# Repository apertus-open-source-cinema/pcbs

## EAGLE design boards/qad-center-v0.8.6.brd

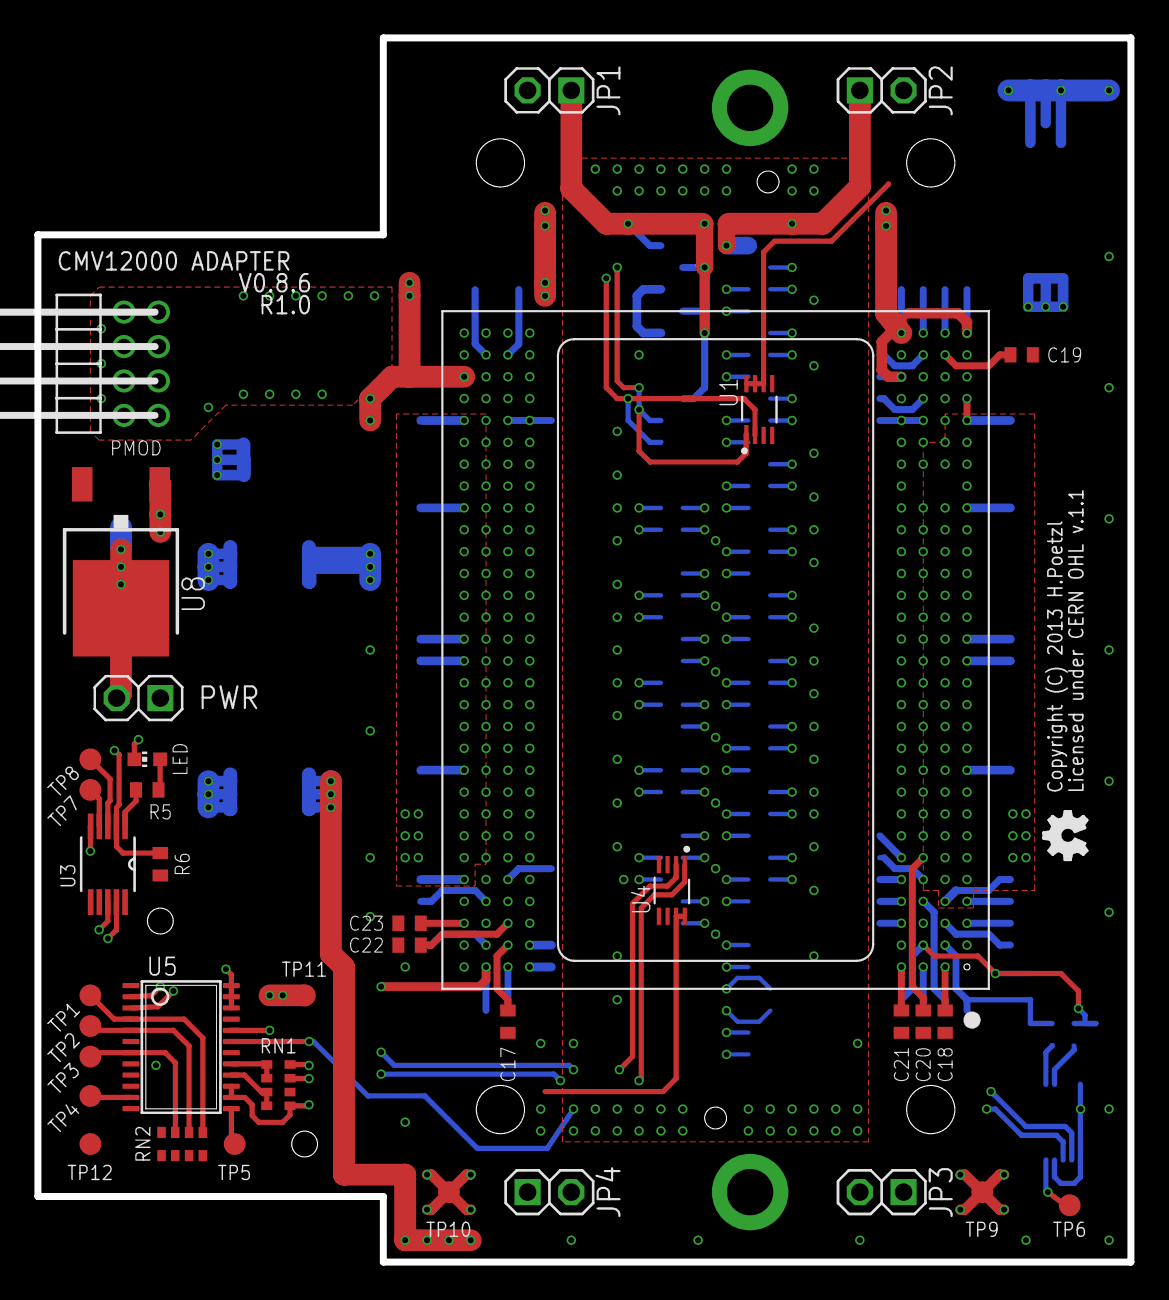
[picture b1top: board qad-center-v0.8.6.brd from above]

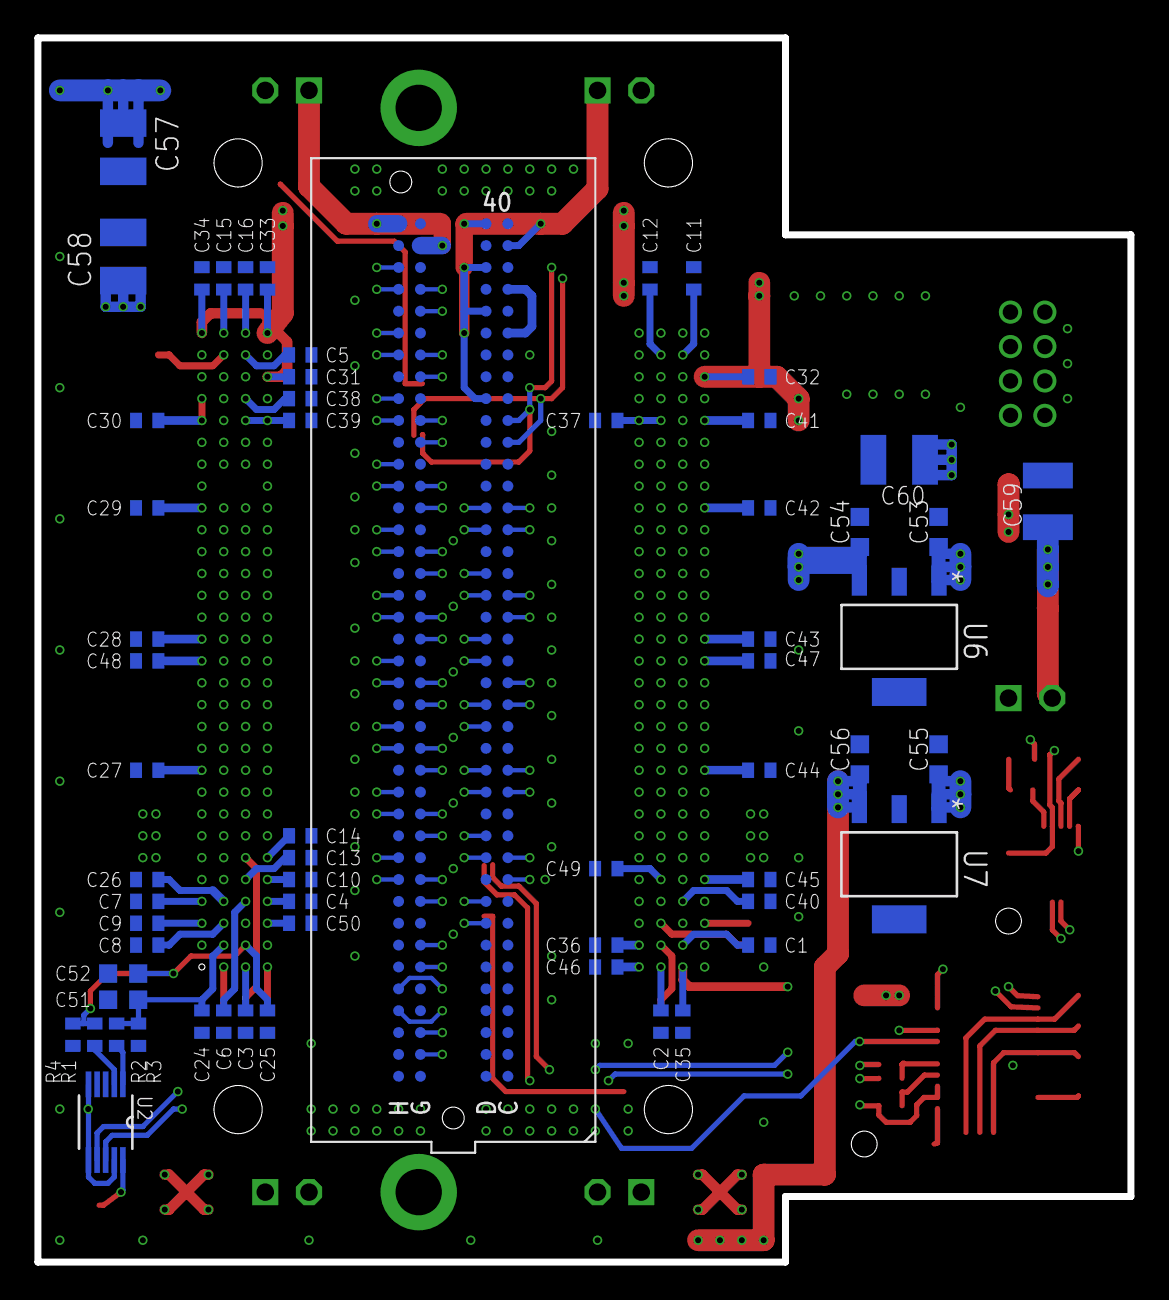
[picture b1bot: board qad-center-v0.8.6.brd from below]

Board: 4 copper layers, 63.5 x 71.1 mm, 98 parts (60 on the bottom side), 130 nets.

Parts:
C1, C2, C3, C4, C5, C6, C7, C8, C9, C10, C11, C12, C13, C14, C15, C16, C17, C18, C19, C20, C21, C22, C23, C24, C25, C26, C27, C28, C29, C30, C32, C33, C34, C35, C36, C37, C38, C39, C40, C41, C42, C43, C44, C45, C46, C47, C48, C49, C50: C0402
C31: 100n; C0402
C51, C52, C53, C54, C55, C56: 10u; C0603K
C57, C58: 100u; C1210
C59, C60: 100u; C1210K
JP1, JP2, JP3, JP4: 1X02-S
LED: RED; CHIP-LED0603
PMOD: PMOD-8; 2X04/90/2MM
PWR: 1X02-S
R1, R2: 1R; R0402
R3, R4: R0402
R5: 220R; R0402
R6: 10k; R0402
RN1, RN2: 10k; CAT16
TP1, TP2, TP3, TP4, TP5, TP6, TP7, TP8, TP9, TP10, TP11, TP12: TPB1,27; B1,27
U1, U4: LM75BGD; SOT996-2/3
U2: AD5647R; SOP50P490X110-10N
U3: PCA9537; TSSOP-10
U5: LM96080; TSSOP24
U6: MCP1826S-3002E/DB; SOT230P700X180-4N
U7: MCP1826S-1802E/DB; SOT230P700X180-4N
U8: AP1084TO252; TO252
U$1: CMV12000ANDON+LM; 10-30-07-237-400T4+LM
U$5: OSHW_FILLX100_NOTEXT
ZED1: FMC-LPC-ZED_NOCCZED; ASP-134604-01-ZED

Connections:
+1V8: C56.1, C57.1, JP2.2, JP3.2, JP4.2, U7.3
+1V8A: C26.1, C27.1, C28.1, C29.1, C30.1, C48.1, JP3.1, TP9.TP, U5.19, U$1.A10, U$1.A15, U$1.A16, U$1.A22, U$1.A26, U$1.A27, U$1.B4
+1V8B: C41.1, C42.1, C43.1, C44.1, C45.1, C46.1, C47.1, JP4.1, TP10.TP, U5.20, U$1.E1, U$1.H5, U$1.H10, U$1.H15, U$1.H16, U$1.H22, U$1.H26
+3V0: C31.1, C32.1, C33.1, C34.1, C35.1, C54.1, RN1.3, TP11.TP, U6.3, U$1.A30, U$1.D28, U$1.D30, U$1.G1, U$1.H28
+3V3: C17.1, C18.1, C19.1, C20.1, C21.1, C22.1, C23.1, C36.1, C37.1, C38.1, C39.1, C40.1, C49.1, C50.1, C53.1, C55.1, C58.1, C60.1, JP1.2, R6.1, RN1.2, RN2.2, RN2.3, RN2.4, TP12.TP, U1.6, U1.7, U1.8, U2.5, U2.6, U2.9, U3.6, U3.10, U4.7, U4.8, U5.1, U5.6, U5.9, U5.12, U6.1, U7.1, U8.2, U$1.C26, U$1.C27, U$1.D3, U$1.D26, U$1.E2, U$1.E26, U$1.F5, U$1.F26, U$1.G4
+5V: C59.1, PWR.2, U8.3
GND: C1.2, C2.2, C3.2, C4.2, C5.2, C6.2, C7.2, C8.2, C9.2, C10.2, C11.2, C12.2, C13.2, C14.2, C15.2, C16.2, C24.2, C25.2, C26.2, C27.2, C28.2, C29.2, C30.2, C31.2, C32.2, C33.2, C34.2, C35.2, C36.2, C37.2, C38.2, C39.2, C40.2, C41.2, C42.2, C43.2, C44.2, C45.2, C46.2, C47.2, C48.2, C49.2, C50.2, C51.2, C52.2, C53.2, C54.2, C55.2, C56.2, C57.2, C58.2, C59.2, C60.2, LED.C, PWR.1, R3.2, R4.2, RN1.1, RN1.4, U1.4, U1.5, U2.3, U2.4, U3.5, U4.4, U4.5, U4.6, U5.8, U5.14, U5.15, U5.18, U5.22, U5.23, U5.24, U6.2, U6.4, U7.2, U7.4, U8.1, U$1.A9, U$1.A21, U$1.A25, U$1.A28, U$1.A29, U$1.B5, U$1.B22, U$1.B26, U$1.B27, U$1.B28, U$1.C15, U$1.C16, U$1.C28, U$1.D2, U$1.D25, U$1.D27, U$1.D29, U$1.E3, U$1.E15, U$1.E16, U$1.E25, U$1.E27, U$1.F27, U$1.G5, U$1.H1, U$1.H6, U$1.H9, U$1.H21, U$1.H25, U$1.H27, ZED1.C1, ZED1.C4, ZED1.C5, ZED1.C8, ZED1.C9, ZED1.C12, ZED1.C13, ZED1.C16, ZED1.C17, ZED1.C20, ZED1.C21, ZED1.C24, ZED1.C25, ZED1.C28, ZED1.C29, ZED1.C32, ZED1.C33, ZED1.C36, ZED1.C38, ZED1.C40, ZED1.D2, ZED1.D3, ZED1.D6, ZED1.D7, ZED1.D10, ZED1.D13, ZED1.D16, ZED1.D19, ZED1.D22, ZED1.D25, ZED1.D28, ZED1.D37, ZED1.D39, ZED1.G1, ZED1.G4, ZED1.G5, ZED1.G8, ZED1.G11, ZED1.G14, ZED1.G17, ZED1.G20, ZED1.G23, ZED1.G26, ZED1.G29, ZED1.G32, ZED1.G35, ZED1.G38, ZED1.G40, ZED1.H3, ZED1.H6, ZED1.H9, ZED1.H12, ZED1.H15, ZED1.H18, ZED1.H21, ZED1.H24, ZED1.H27, ZED1.H30, ZED1.H33, ZED1.H36, ZED1.H39
unnamed: C17.2, U$1.F2
unnamed: C18.2, U$1.B1
unnamed: C19.2, U$1.B29
unnamed: C20.2, U$1.C6
unnamed: C21.2, U$1.D1
unnamed: C22.2, U$1.F3
unnamed: C23.2, U$1.H3
unnamed: C1.1, U$1.G2
unnamed: C2.1, U$1.F1
unnamed: C3.1, U$1.C1
unnamed: C4.1, U$1.D4
unnamed: C5.1, U$1.C29
unnamed: C6.1, U$1.C4
unnamed: C7.1, U$1.A4
unnamed: C8.1, U$1.B3
unnamed: C9.1, U$1.A3
unnamed: C10.1, U$1.D5
unnamed: C11.1, U$1.G29
unnamed: C12.1, U$1.F29
unnamed: C13.1, U$1.C5
unnamed: C14.1, U$1.D6
unnamed: C15.1, U$1.B30
unnamed: C16.1, U$1.C30
unnamed: U$1.B6, ZED1.H11
unnamed: U$1.B7, ZED1.H10
unnamed: PMOD.1, U$1.F28
unnamed: U$1.D7, ZED1.D12
unnamed: U$1.D8, ZED1.D11
unnamed: PMOD.8, U$1.H29
unnamed: PMOD.2, U$1.E28
unnamed: PMOD.7, U$1.G28
unnamed: PMOD.10, U$1.E30
unnamed: PMOD.4, U$1.G30
unnamed: U$1.B8, ZED1.H14
unnamed: U$1.C9, ZED1.D15
unnamed: U$1.C10, ZED1.D14
unnamed: ZED1.C35, ZED1.C37
unnamed: JP1.1, ZED1.C39, ZED1.D32, ZED1.D36, ZED1.D38, ZED1.D40
unnamed: JP2.1, ZED1.G39, ZED1.H40
unnamed: R1.2, U2.2
unnamed: U$1.G10, ZED1.G13
unnamed: U$1.A11, ZED1.D18
unnamed: U$1.A12, ZED1.D17
unnamed: U$1.C11, ZED1.H17
unnamed: U$1.C12, ZED1.H16
unnamed: U$1.A13, ZED1.D21
unnamed: U$1.A14, ZED1.D20
unnamed: U$1.D13, ZED1.H20
unnamed: U$1.D14, ZED1.H19
unnamed: U$1.F16, ZED1.G22
unnamed: U$1.F17, ZED1.G21
unnamed: U$1.A17, ZED1.H26
unnamed: U$1.A18, ZED1.H25
unnamed: U$1.C17, ZED1.D24
unnamed: U$1.C18, ZED1.D23
unnamed: U$1.A19, ZED1.H29
unnamed: U$1.A20, ZED1.H28
unnamed: U$1.C19, ZED1.D27
unnamed: U$1.C20, ZED1.D26
unnamed: U$1.D21, ZED1.H32
unnamed: U$1.D22, ZED1.H31
unnamed: U$1.A23, ZED1.H35
unnamed: U$1.A24, ZED1.H34
unnamed: U$1.B24, ZED1.H38
unnamed: U$1.B25, ZED1.H37
unnamed: U$1.D15, ZED1.H23
unnamed: U$1.D16, ZED1.H22
unnamed: U$1.G22, ZED1.G34
unnamed: U$1.G23, ZED1.G33
unnamed: U$1.E22, ZED1.G30
unnamed: U$1.E21, ZED1.G31
unnamed: U$1.F21, ZED1.G27
unnamed: U$1.F20, ZED1.G28
unnamed: U$1.E20, ZED1.C26
unnamed: U$1.E19, ZED1.C27
unnamed: U$1.F19, ZED1.G24
unnamed: U$1.F18, ZED1.G25
unnamed: U$1.E18, ZED1.C22
unnamed: U$1.E17, ZED1.C23
unnamed: U$1.H23, ZED1.G37
unnamed: U$1.H24, ZED1.G36
unnamed: U$1.G15, ZED1.G18
unnamed: U$1.G14, ZED1.G19
unnamed: U$1.H14, ZED1.C18
unnamed: U$1.H13, ZED1.C19
unnamed: U$1.G13, ZED1.G15
unnamed: U$1.G12, ZED1.G16
unnamed: U$1.H12, ZED1.C14
unnamed: U$1.H11, ZED1.C15
unnamed: U$1.G11, ZED1.G12
unnamed: U$1.B9, ZED1.H13
unnamed: U$1.F9, ZED1.C10
unnamed: U$1.F8, ZED1.C11
unnamed: U$1.E8, ZED1.G9
unnamed: U$1.E7, ZED1.G10
unnamed: U$1.F7, ZED1.G6
unnamed: U$1.F6, ZED1.G7
unnamed: U$1.E5, ZED1.H5
unnamed: U$1.E6, ZED1.H4
unnamed: U$1.G6, ZED1.G3
unnamed: U$1.G7, ZED1.G2
unnamed: U$1.A5, ZED1.D9
unnamed: U$1.A6, ZED1.D8
unnamed: PMOD.9, U$1.H30
unnamed: PMOD.3, U$1.E29
unnamed: RN2.5, TP1.TP, U5.4
unnamed: R6.2, U3.2, U$1.F30
unnamed: R5.1, U3.1
unnamed: RN2.6, TP2.TP, U5.5
unnamed: TP8.TP, U3.3
unnamed: TP7.TP, U3.4
unnamed: RN1.5, RN1.6, U5.17
unnamed: RN2.7, TP3.TP, U5.7
unnamed: TP4.TP, U5.11
unnamed: TP5.TP, U5.13
unnamed: RN1.7, RN1.8, U5.16
unnamed: R2.2, U2.1
unnamed: LED.A, R5.2
unnamed: TP6.TP, U2.10
SCL: U1.2, U2.7, U3.8, U4.2, U5.3, ZED1.C30
SDA: U1.1, U2.8, U3.9, U4.1, U5.2, ZED1.C31
VTREF: C24.1, C51.1, R2.1, R3.1, U$1.B2
VTSIG: C25.1, C52.1, R1.1, R4.1, U$1.C2

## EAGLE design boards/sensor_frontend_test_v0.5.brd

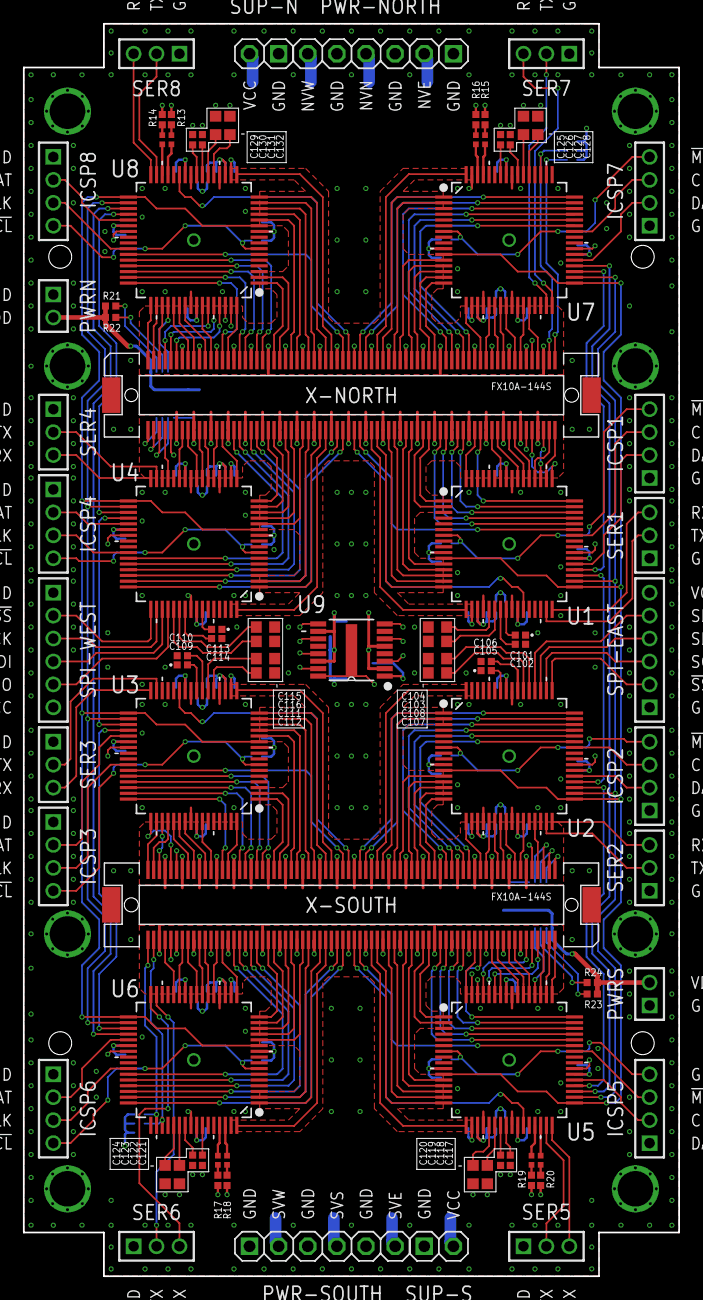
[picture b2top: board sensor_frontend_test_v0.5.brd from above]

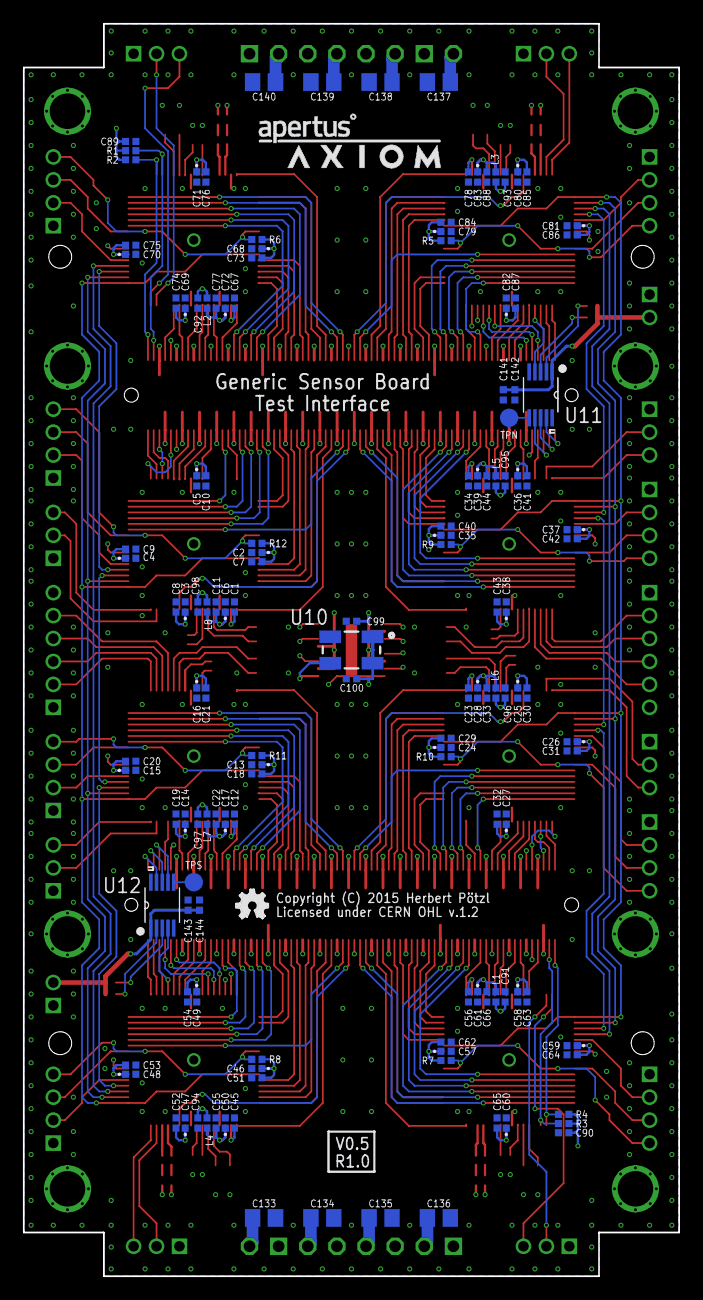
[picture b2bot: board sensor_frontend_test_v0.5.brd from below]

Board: 4 copper layers, 57.1 x 109.2 mm, 223 parts (140 on the bottom side), 345 nets.

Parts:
C1, C2, C3, C4, C5, C6, C7, C8, C9, C10, C11, C12, C13, C14, C15, C16, C17, C18, C19, C20, C21, C22, C23, C24, C25, C26, C27, C28, C29, C30, C31, C32, C33, C34, C35, C36, C37, C38, C39, C40, C41, C42, C43, C44, C45, C46, C47, C48, C49, C50, C51, C52, C53, C54, C55, C56, C57, C58, C59, C60, C61, C62, C63, C64, C65, C66, C67, C68, C69, C70, C71, C72, C73, C74, C75, C76, C77, C78, C79, C80, C81, C82, C83, C84, C85, C86, C87, C88, C89, C90, C91, C92, C93, C94, C95, C96, C97, C98, C99, C100, C101, C102, C105, C106, C109, C110, C113, C114, C117, C118, C121, C122, C125, C126, C129, C130, C141, C142, C143, C144: 0402-B
C103, C104, C107, C108, C111, C112, C115, C116, C119, C120, C123, C124, C127, C128, C131, C132: 0603-B
C133, C134, C135, C136, C137, C138, C139, C140: 0805-A
ICSP1, ICSP2, ICSP3, ICSP4, ICSP5, ICSP6, ICSP7, ICSP8: 1X04M
L1, L2, L3, L4, L5, L6, L7, L8: 0402-B
LED1, LED2, LED3, LED4: DUAL-LED-0404; 0404
LOGO1: OSHW_LOGO_FILLX0100-NT; OSHW_FILLX100_NOTEXT
PWR-NORTH: 1X06-S
PWR-SOUTH: 1X06-S
PWRN: 1X02M
PWRS: 1X02M
R1, R2, R3, R4, R5, R6, R7, R8, R9, R10, R11, R12, R13, R14, R15, R16, R17, R18, R19, R20, R21, R22, R23, R24: 0402-B
SER1, SER2, SER3, SER4, SER5, SER6, SER7, SER8: 1X03M
SPI-EAST: 1X06M
SPI-WEST: 1X06M
SUP-N: 1X02-S
SUP-S: 1X02-S
TPN: TPTP16R; TP16R
TPS: TPTP16R; TP16R
U1, U2, U3, U4, U5, U6, U7, U8: PIC16F1526-I/PT; QFP50P1200X1200X120-64N
U9: SI53365; SOP65P640X120-16N
U10: OSCILLATOR5X3-PIN1-INDICATED; CRYSTAL-OSC-SMD-5X3
U11, U12: MCP4728-E/UN; SOP50P490X110-10N
U$2: APERTUS_LOGO334X100; APERTUS_LOGO_334X100
U$3: AXIOM_LOGO525X80; AXIOM_LOGO_525X80
X-NORTH: FX10-144S; FX10A-144S
X-SOUTH: FX10-144S; FX10A-144S

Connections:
!E_SS: U1.11, U1.33, U2.11, U2.33, U5.11, U5.33, U7.11, U7.33
!LDAC_N: U8.52, U11.4
!LDAC_S: U5.52, U12.4
!MCLR1!: ICSP1.4, R12.2, U1.7
!MCLR2!: ICSP2.4, R11.2, U2.7
!MCLR3!: ICSP3.4, R10.2, U3.7
!MCLR4!: ICSP4.4, R9.2, U4.7
!MCLR5!: ICSP5.4, R8.2, U5.7
!MCLR6!: ICSP6.4, R7.2, U6.7
!MCLR7!: ICSP7.4, R6.2, U7.7
!MCLR8!: ICSP8.4, R5.2, U8.7
!W_SS: U3.11, U3.33, U4.11, U4.33, U6.11, U6.33, U8.11, U8.33
AVCC1: C6.1, C11.1, L8.2, U1.19
AVCC2: C17.1, C22.1, L7.2, U2.19
AVCC3: C28.1, C33.1, L6.2, U3.19
AVCC4: C39.1, C44.1, L5.2, U4.19
AVCC5: C50.1, C55.1, L4.2, U5.19
AVCC6: C61.1, C66.1, L1.2, U6.19
AVCC7: C72.1, C77.1, L2.2, U7.19
AVCC8: C83.1, C88.1, L3.2, U8.19
CAP1A: C101.1, U1.24
CAP1B: C102.1, U1.23
CAP1C: C103.1, U1.22
CAP1D: C104.1, U1.21
CAP2A: C105.1, U2.58
CAP2B: C106.1, U2.55
CAP2C: C107.1, U2.54
CAP2D: C108.1, U2.53
CAP3A: C109.1, U3.24
CAP3B: C110.1, U3.23
CAP3C: C111.1, U3.22
CAP3D: C112.1, U3.21
CAP4A: C113.1, U4.58
CAP4B: C114.1, U4.55
CAP4C: C115.1, U4.54
CAP4D: C116.1, U4.53
CAP5A: C117.1, U5.24
CAP5B: C118.1, U5.23
CAP5C: C119.1, U5.22
CAP5D: C120.1, U5.21
CAP6A: C121.1, U6.58
CAP6B: C122.1, U6.55
CAP6C: C123.1, U6.54
CAP6D: C124.1, U6.53
CAP7A: C125.1, U7.58
CAP7B: C126.1, U7.55
CAP7C: C127.1, U7.54
CAP7D: C128.1, U7.53
CAP8A: C129.1, U8.24
CAP8B: C130.1, U8.23
CAP8C: C131.1, U8.22
CAP8D: C132.1, U8.21
CLKIN1: U1.39, U9.8
CLKIN2: U2.39, U9.16
CLKIN3: U3.39, U9.15
CLKIN4: U4.39, U9.9
CLKIN5: U5.39, U9.3
CLKIN6: U6.39, U9.13
CLKIN7: U7.39, U9.6
CLKIN8: U8.39, U9.11
E_SCK: U1.34, U2.34, U5.34, U7.34
E_SD_17: U1.36, U7.35
E_SD_21: U1.35, U2.36
E_SD_52: U2.35, U5.36
E_SD_75: U5.35, U7.36
GND: C1.2, C2.2, C3.2, C4.2, C5.2, C6.2, C7.2, C8.2, C9.2, C10.2, C11.2, C12.2, C13.2, C14.2, C15.2, C16.2, C17.2, C18.2, C19.2, C20.2, C21.2, C22.2, C23.2, C24.2, C25.2, C26.2, C27.2, C28.2, C29.2, C30.2, C31.2, C32.2, C33.2, C34.2, C35.2, C36.2, C37.2, C38.2, C39.2, C40.2, C41.2, C42.2, C43.2, C44.2, C45.2, C46.2, C47.2, C48.2, C49.2, C50.2, C51.2, C52.2, C53.2, C54.2, C55.2, C56.2, C57.2, C58.2, C59.2, C60.2, C61.2, C62.2, C63.2, C64.2, C65.2, C66.2, C67.2, C68.2, C69.2, C70.2, C71.2, C72.2, C73.2, C74.2, C75.2, C76.2, C77.2, C78.2, C79.2, C80.2, C81.2, C82.2, C83.2, C84.2, C85.2, C86.2, C87.2, C88.2, C89.2, C90.2, C91.2, C92.2, C93.2, C94.2, C95.2, C96.2, C97.2, C98.2, C99.2, C100.2, C101.2, C102.2, C103.2, C104.2, C105.2, C106.2, C107.2, C108.2, C109.2, C110.2, C111.2, C112.2, C113.2, C114.2, C115.2, C116.2, C117.2, C118.2, C119.2, C120.2, C121.2, C122.2, C123.2, C124.2, C125.2, C126.2, C127.2, C128.2, C129.2, C130.2, C131.2, C132.2, C133.2, C134.2, C135.2, C136.2, C137.2, C138.2, C139.2, C140.2, C141.2, C142.2, C143.2, C144.2, ICSP1.1, ICSP2.1, ICSP3.1, ICSP4.1, ICSP5.1, ICSP6.1, ICSP7.1, ICSP8.1, PWR-NORTH.1, PWR-NORTH.3, PWR-NORTH.5, PWR-SOUTH.1, PWR-SOUTH.3, PWR-SOUTH.5, PWRN.1, PWRS.1, SER1.1, SER2.1, SER3.1, SER4.1, SER5.1, SER6.1, SER7.1, SER8.1, SPI-EAST.1, SPI-WEST.1, SUP-N.1, SUP-S.1, U1.9, U1.20, U1.25, U1.41, U1.56, U2.9, U2.20, U2.25, U2.41, U2.56, U3.9, U3.20, U3.25, U3.41, U3.56, U4.9, U4.20, U4.25, U4.41, U4.56, U5.9, U5.20, U5.25, U5.41, U5.56, U6.9, U6.20, U6.25, U6.41, U6.56, U7.9, U7.20, U7.25, U7.41, U7.56, U7.63, U8.9, U8.20, U8.25, U8.41, U8.56, U9.4, U9.7, U9.12, U10.2, U11.10, U12.10, X-NORTH.12, X-NORTH.18, X-NORTH.24, X-NORTH.30, X-NORTH.36, X-NORTH.42, X-NORTH.43, X-NORTH.48, X-NORTH.54, X-NORTH.60, X-NORTH.66, X-NORTH.72, X-NORTH.78, X-NORTH.84, X-NORTH.90, X-NORTH.96, X-NORTH.102, X-NORTH.103, X-NORTH.108, X-NORTH.114, X-NORTH.120, X-NORTH.126, X-NORTH.132, X-NORTH.138, X-NORTH.139, X-SOUTH.12, X-SOUTH.18, X-SOUTH.24, X-SOUTH.30, X-SOUTH.36, X-SOUTH.42, X-SOUTH.43, X-SOUTH.48, X-SOUTH.54, X-SOUTH.60, X-SOUTH.66, X-SOUTH.72, X-SOUTH.78, X-SOUTH.84, X-SOUTH.90, X-SOUTH.96, X-SOUTH.102, X-SOUTH.103, X-SOUTH.108, X-SOUTH.114, X-SOUTH.120, X-SOUTH.126, X-SOUTH.132, X-SOUTH.138, X-SOUTH.139
ICSPCLK1: ICSP1.3, U1.42
ICSPCLK2: ICSP2.3, U2.42
ICSPCLK3: ICSP3.3, U3.42
ICSPCLK4: ICSP4.3, U4.42
ICSPCLK5: ICSP5.3, U5.42
ICSPCLK6: ICSP6.3, U6.42
ICSPCLK7: ICSP7.3, U7.42
ICSPCLK8: ICSP8.3, U8.42
ICSPDAT1: ICSP1.2, U1.37
ICSPDAT2: ICSP2.2, U2.37
ICSPDAT3: ICSP3.2, U3.37
ICSPDAT4: ICSP4.2, U4.37
ICSPDAT5: ICSP5.2, U5.37
ICSPDAT6: ICSP6.2, U6.37
ICSPDAT7: ICSP7.2, U7.37
ICSPDAT8: ICSP8.2, U8.37
LED5: LED4.4, U5.29
LED5B: LED4.3, U5.30
LED6: LED3.4, U6.61
LED6B: LED3.3, U6.62
LED7: LED2.4, U7.61
LED7B: LED2.3, U7.62
LED8: LED1.4, U8.29
LED8B: LED1.3, U8.30
N00_N: U4.24, X-NORTH.16
N00_P: U4.27, X-NORTH.14
N01_N: U8.54, X-NORTH.17
N01_P: U8.53, X-NORTH.15
N02_N: U4.22, X-NORTH.22
N02_P: U4.23, X-NORTH.20
N03_N: U8.58, X-NORTH.23
N03_P: U8.55, X-NORTH.21
N04_N: U4.17, X-NORTH.28
N04_P: U4.21, X-NORTH.26
N05_N: U8.64, X-NORTH.29
N05_P: U8.48, X-NORTH.27
N06_N: U4.44, X-NORTH.34
N06_P: U4.43, X-NORTH.32
N07_N: U8.46, X-NORTH.35
N07_P: U8.47, X-NORTH.33
N08_N: U4.46, X-NORTH.40
N08_P: U4.45, X-NORTH.38
N09_N: U8.44, X-NORTH.41
N09_P: U8.45, X-NORTH.39
N10_N: U4.15, X-NORTH.46
N10_P: U4.16, X-NORTH.44
N11_N: U8.2, X-NORTH.47
N11_P: U8.1, X-NORTH.45
N12_N: U4.13, X-NORTH.52
N12_P: U4.14, X-NORTH.50
N13_N: U8.13, X-NORTH.53
N13_P: U8.12, X-NORTH.51
N14_N: U4.2, X-NORTH.58
N14_P: U4.12, X-NORTH.56
N15_N: U8.15, X-NORTH.59
N15_P: U8.14, X-NORTH.57
N16_N: U4.64, X-NORTH.64
N16_P: U4.1, X-NORTH.62
N17_N: U8.17, X-NORTH.65
N17_P: U8.16, X-NORTH.63
N18_N: U4.48, X-NORTH.70
N18_P: U4.47, X-NORTH.68
N19_N: U8.27, X-NORTH.71
N19_P: U8.43, X-NORTH.69
N20_N: U1.43, X-NORTH.76
N20_P: U1.27, X-NORTH.74
N21_N: U7.47, X-NORTH.77
N21_P: U7.48, X-NORTH.75
N22_N: U1.16, X-NORTH.82
N22_P: U1.17, X-NORTH.80
N23_N: U7.1, X-NORTH.83
N23_P: U7.64, X-NORTH.81
N24_N: U1.14, X-NORTH.88
N24_P: U1.15, X-NORTH.86
N25_N: U7.12, X-NORTH.89
N25_P: U7.2, X-NORTH.87
N26_N: U1.12, X-NORTH.94
N26_P: U1.13, X-NORTH.92
N27_N: U7.14, X-NORTH.95
N27_P: U7.13, X-NORTH.93
N28_N: U1.1, X-NORTH.100
N28_P: U1.2, X-NORTH.98
N29_N: U7.16, X-NORTH.101
N29_P: U7.15, X-NORTH.99
N30_N: U1.45, X-NORTH.106
N30_P: U1.44, X-NORTH.104
N31_N: U7.45, X-NORTH.107
N31_P: U7.46, X-NORTH.105
N32_N: U1.47, X-NORTH.112
N32_P: U1.46, X-NORTH.110
N33_N: U7.43, X-NORTH.113
N33_P: U7.44, X-NORTH.111
N34_N: U1.48, X-NORTH.118
N34_P: U1.64, X-NORTH.116
N35_N: U7.21, X-NORTH.119
N35_P: U7.17, X-NORTH.117
N36_N: U1.55, X-NORTH.124
N36_P: U1.58, X-NORTH.122
N37_N: U7.23, X-NORTH.125
N37_P: U7.22, X-NORTH.123
N38_N: U1.53, X-NORTH.130
N38_P: U1.54, X-NORTH.128
N39_N: U7.27, X-NORTH.131
N39_P: U7.24, X-NORTH.129
unnamed: C45.1, U5.18
unnamed: U9.1, U10.3
unnamed: TPS.TP, U12.6
unnamed: C1.1, U1.18
unnamed: LED1.1, R13.2
unnamed: LED1.2, R14.2
unnamed: LED2.1, R15.2
unnamed: LED2.2, R16.2
unnamed: LED3.1, R17.2
unnamed: LED3.2, R18.2
unnamed: LED4.1, R19.2
unnamed: LED4.2, R20.2
unnamed: TPN.TP, U11.6
unnamed: C56.1, U6.18
unnamed: C12.1, U2.18
unnamed: C23.1, U3.18
unnamed: C34.1, U4.18
unnamed: C67.1, U7.18
unnamed: C78.1, U8.18
N_CHK_EN: U4.29, X-NORTH.8
N_CHK_V: C141.1, C142.1, PWRN.2, R21.1, R22.1, U11.1, X-NORTH.10
N_I2C_EN: U7.28, X-NORTH.137
N_SCK: U1.50, X-NORTH.144
N_SCL: R2.2, U7.50, X-NORTH.143
N_SDA: R1.2, U7.51, X-NORTH.141
N_SDI: U1.51, X-NORTH.140
N_SDO: U1.52, X-NORTH.142
N_SPI_EN: U1.49, X-NORTH.136
N_VE: C140.1, PWR-NORTH.2, X-NORTH.109, X-NORTH.115, X-NORTH.127, X-NORTH.133
N_VE_CV: U11.7, X-NORTH.6
N_VE_OV: U8.51, X-NORTH.5
N_VE_UV: U8.61, X-NORTH.11
N_VN: C139.1, PWR-NORTH.4, X-NORTH.49, X-NORTH.55, X-NORTH.61, X-NORTH.67, X-NORTH.79, X-NORTH.85, X-NORTH.91, X-NORTH.97
N_VN_CV: U11.8, X-NORTH.4
N_VN_OV: U8.50, X-NORTH.3
N_VN_UV: U8.60, X-NORTH.9
N_VW: C138.1, PWR-NORTH.6, X-NORTH.13, X-NORTH.19, X-NORTH.31, X-NORTH.37
N_VW_CV: U11.9, X-NORTH.2
N_VW_OV: U8.49, X-NORTH.1
N_VW_UV: U8.59, X-NORTH.7
RX1: SER1.3, U1.32
RX2: SER2.3, U2.32
RX3: SER3.3, U3.32
RX4: SER4.3, U4.32
RX5: SER5.3, U5.32
RX6: SER6.3, U6.32
RX7: SER7.3, U7.32
RX8: SER8.3, U8.32
S00_N: U2.24, X-SOUTH.16
S00_P: U2.27, X-SOUTH.14
S01_N: U5.54, X-SOUTH.17
S01_P: U5.53, X-SOUTH.15
S02_N: U2.22, X-SOUTH.22
S02_P: U2.23, X-SOUTH.20
S03_N: U5.58, X-SOUTH.23
S03_P: U5.55, X-SOUTH.21
S04_N: U2.17, X-SOUTH.28
S04_P: U2.21, X-SOUTH.26
S05_N: U5.64, X-SOUTH.29
S05_P: U5.48, X-SOUTH.27
S06_N: U2.44, X-SOUTH.34
S06_P: U2.43, X-SOUTH.32
S07_N: U5.46, X-SOUTH.35
S07_P: U5.47, X-SOUTH.33
S08_N: U2.46, X-SOUTH.40
S08_P: U2.45, X-SOUTH.38
S09_N: U5.44, X-SOUTH.41
S09_P: U5.45, X-SOUTH.39
S10_N: U2.15, X-SOUTH.46
S10_P: U2.16, X-SOUTH.44
S11_N: U5.2, X-SOUTH.47
S11_P: U5.1, X-SOUTH.45
S12_N: U2.13, X-SOUTH.52
S12_P: U2.14, X-SOUTH.50
S13_N: U5.13, X-SOUTH.53
S13_P: U5.12, X-SOUTH.51
S14_N: U2.2, X-SOUTH.58
S14_P: U2.12, X-SOUTH.56
S15_N: U5.15, X-SOUTH.59
S15_P: U5.14, X-SOUTH.57
S16_N: U2.64, X-SOUTH.64
S16_P: U2.1, X-SOUTH.62
S17_N: U5.17, X-SOUTH.65
S17_P: U5.16, X-SOUTH.63
S18_N: U2.48, X-SOUTH.70
S18_P: U2.47, X-SOUTH.68
S19_N: U5.27, X-SOUTH.71
S19_P: U5.43, X-SOUTH.69
S20_N: U3.43, X-SOUTH.76
S20_P: U3.27, X-SOUTH.74
S21_N: U6.47, X-SOUTH.77
S21_P: U6.48, X-SOUTH.75
S22_N: U3.16, X-SOUTH.82
S22_P: U3.17, X-SOUTH.80
S23_N: U6.1, X-SOUTH.83
S23_P: U6.64, X-SOUTH.81
S24_N: U3.14, X-SOUTH.88
S24_P: U3.15, X-SOUTH.86
S25_N: U6.12, X-SOUTH.89
S25_P: U6.2, X-SOUTH.87
S26_N: U3.12, X-SOUTH.94
S26_P: U3.13, X-SOUTH.92
S27_N: U6.14, X-SOUTH.95
S27_P: U6.13, X-SOUTH.93
S28_N: U3.1, X-SOUTH.100
S28_P: U3.2, X-SOUTH.98
S29_N: U6.16, X-SOUTH.101
S29_P: U6.15, X-SOUTH.99
S30_N: U3.45, X-SOUTH.106
S30_P: U3.44, X-SOUTH.104
S31_N: U6.45, X-SOUTH.107
S31_P: U6.46, X-SOUTH.105
S32_N: U3.47, X-SOUTH.112
S32_P: U3.46, X-SOUTH.110
S33_N: U6.43, X-SOUTH.113
S33_P: U6.44, X-SOUTH.111
S34_N: U3.48, X-SOUTH.118
S34_P: U3.64, X-SOUTH.116
S35_N: U6.21, X-SOUTH.119
S35_P: U6.17, X-SOUTH.117
S36_N: U3.55, X-SOUTH.124
S36_P: U3.58, X-SOUTH.122
S37_N: U6.23, X-SOUTH.125
S37_P: U6.22, X-SOUTH.123
S38_N: U3.53, X-SOUTH.130
S38_P: U3.54, X-SOUTH.128
S39_N: U6.27, X-SOUTH.131
S39_P: U6.24, X-SOUTH.129
SCK2B: SPI-EAST.3, U2.50
SCK4B: SPI-WEST.3, U4.50
SCL_N: R21.2, U8.63, U11.2
SCL_S: R23.2, U5.63, U12.2
SDA_N: R22.2, U8.62, U11.3
SDA_S: R24.2, U5.62, U12.3
SDI2B: SPI-EAST.4, U2.51
SDI4B: SPI-WEST.4, U4.51
SDO2B: SPI-EAST.5, U2.52
SDO4B: SPI-WEST.5, U4.52
SS2B: SPI-EAST.2, U2.49
SS4B: SPI-WEST.2, U4.49
S_CHK_EN: U2.29, X-SOUTH.8
S_CHK_V: C143.1, C144.1, PWRS.2, R23.1, R24.1, U12.1, X-SOUTH.10
S_I2C_EN: U6.28, X-SOUTH.137
S_SCK: U3.50, X-SOUTH.144
S_SCL: R4.2, U6.50, X-SOUTH.143
S_SDA: R3.2, U6.51, X-SOUTH.141
S_SDI: U3.51, X-SOUTH.140
S_SDO: U3.52, X-SOUTH.142
S_SPI_EN: U3.49, X-SOUTH.136
S_VE: C134.1, PWR-SOUTH.6, X-SOUTH.13, X-SOUTH.19, X-SOUTH.31, X-SOUTH.37
S_VE_CV: U12.9, X-SOUTH.2
S_VE_OV: U5.49, X-SOUTH.1
S_VE_UV: U5.59, X-SOUTH.7
S_VS: C135.1, PWR-SOUTH.4, X-SOUTH.49, X-SOUTH.55, X-SOUTH.61, X-SOUTH.67, X-SOUTH.79, X-SOUTH.85, X-SOUTH.91, X-SOUTH.97
S_VS_CV: U12.8, X-SOUTH.4
S_VS_OV: U5.50, X-SOUTH.3
S_VS_UV: U5.60, X-SOUTH.9
S_VW: C136.1, PWR-SOUTH.2, X-SOUTH.109, X-SOUTH.115, X-SOUTH.127, X-SOUTH.133
S_VW_CV: U12.7, X-SOUTH.6
S_VW_OV: U5.51, X-SOUTH.5
S_VW_UV: U5.61, X-SOUTH.11
TX1: SER1.2, U1.31
TX2: SER2.2, U2.31
TX3: SER3.2, U3.31
TX4: SER4.2, U4.31
TX5: SER5.2, U5.31
TX6: SER6.2, U6.31
TX7: SER7.2, U7.31
TX8: SER8.2, U8.31
VCC: C2.1, C3.1, C4.1, C5.1, C7.1, C8.1, C9.1, C10.1, C13.1, C14.1, C15.1, C16.1, C18.1, C19.1, C20.1, C21.1, C24.1, C25.1, C26.1, C27.1, C29.1, C30.1, C31.1, C32.1, C35.1, C36.1, C37.1, C38.1, C40.1, C41.1, C42.1, C43.1, C46.1, C47.1, C48.1, C49.1, C51.1, C52.1, C53.1, C54.1, C57.1, C58.1, C59.1, C60.1, C62.1, C63.1, C64.1, C65.1, C68.1, C69.1, C70.1, C71.1, C73.1, C74.1, C75.1, C76.1, C79.1, C80.1, C81.1, C82.1, C84.1, C85.1, C86.1, C87.1, C89.1, C90.1, C91.1, C92.1, C93.1, C94.1, C95.1, C96.1, C97.1, C98.1, C99.1, C100.1, C133.1, C137.1, L1.1, L2.1, L3.1, L4.1, L5.1, L6.1, L7.1, L8.1, R1.1, R2.1, R3.1, R4.1, R5.1, R6.1, R7.1, R8.1, R9.1, R10.1, R11.1, R12.1, R13.1, R14.1, R15.1, R16.1, R17.1, R18.1, R19.1, R20.1, SPI-EAST.6, SPI-WEST.6, SUP-N.2, SUP-S.2, U1.10, U1.26, U1.38, U1.57, U2.10, U2.26, U2.38, U2.57, U3.10, U3.26, U3.38, U3.57, U4.10, U4.26, U4.38, U4.57, U5.10, U5.26, U5.38, U5.57, U6.10, U6.26, U6.38, U6.57, U7.10, U7.26, U7.38, U7.57, U8.10, U8.26, U8.38, U8.57, U9.2, U9.5, U9.10, U9.14, U10.1, U10.4
W_SCK: U3.34, U4.34, U6.34, U8.34
W_SD_36: U3.36, U6.35
W_SD_43: U3.35, U4.36
W_SD_68: U6.36, U8.35
W_SD_84: U4.35, U8.36

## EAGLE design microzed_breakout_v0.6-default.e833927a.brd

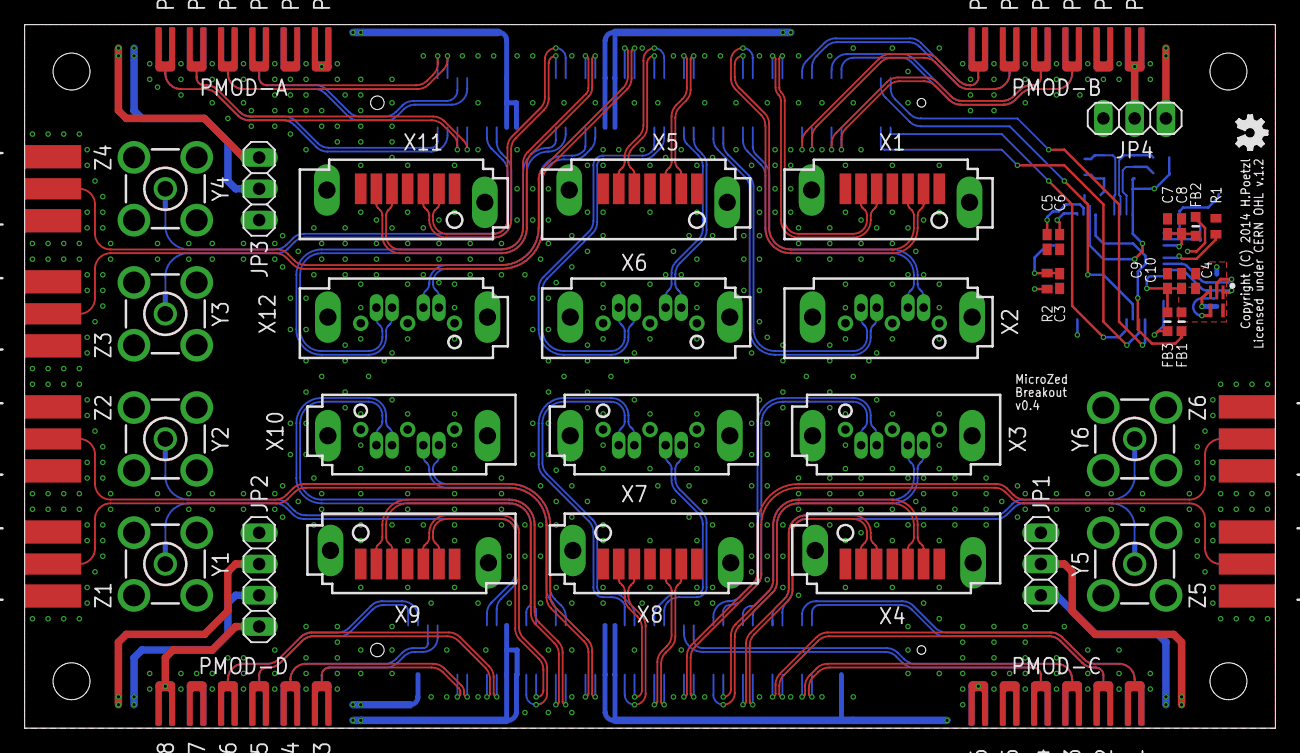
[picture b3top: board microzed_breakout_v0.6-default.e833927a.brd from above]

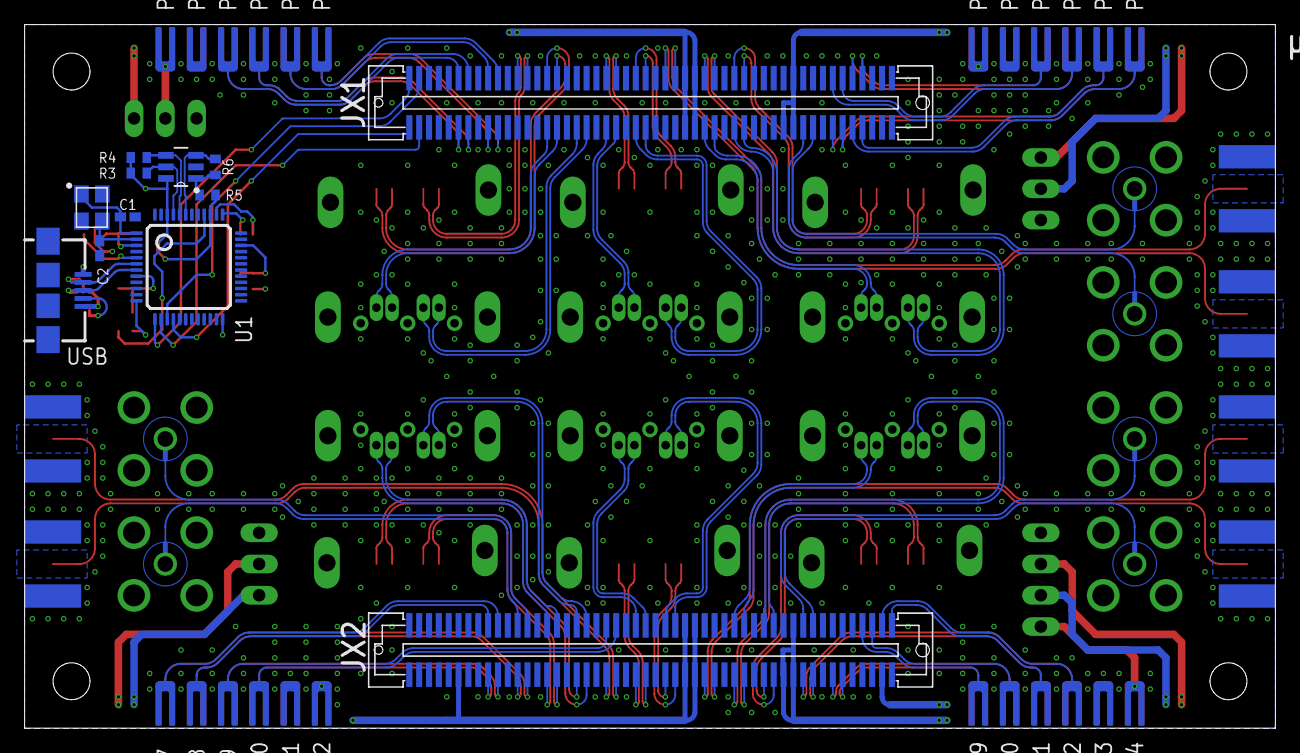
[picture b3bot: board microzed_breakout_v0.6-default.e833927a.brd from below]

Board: 4 copper layers, 101.6 x 57.1 mm, 102 parts (35 on the bottom side), 123 nets.

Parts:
C1, C2: C0402K
C3: 10n; C0402K
C4, C5, C6, C8, C10: 100n; C0402K
C7, C9: 4µ7; C0402K
FB1, FB2, FB3: 600R; _0603MP
JP1, JP3, JP4: 1X03
JP2: 1X04
LOGO1: OSHW_LOGO_FILLX0100-NT; OSHW_FILLX100_NOTEXT
PAD1, PAD2, PAD3, PAD4, PAD5, PAD6, PAD7, PAD8, PAD9, PAD10, PAD11, PAD12, PAD13, PAD14, PAD15, PAD16, PAD17, PAD18, PAD19, PAD20, PAD21, PAD22, PAD23, PAD24, PAD25, PAD26, PAD27, PAD28, PAD29, PAD30, PAD31, PAD32, PAD33, PAD34, PAD35, PAD36, PAD37, PAD38, PAD39, PAD40, PAD41, PAD42, PAD43, PAD44, PAD45, PAD46, PAD47, PAD48: 1.6X3.8U-MM
Q1: SMD-4P-2G-3.2X2.5; ABM8G
R1: 12k; R0402
R2, R3, R4, R5: 10k; R0402
R6: 2k; R0402
U1: FT232H; LQFP48
U2: 93LC46BT-I/OT; SOT95P280X145-6N
U3: TPD3E001DRLR; SOT50P160X60-5N
USB: USB-AB-MICRO-SMD
X1, X4, X5, X8, X9, X11: SATA7-SMD-VERT
X2, X3, X6, X7, X10, X12: SATA7-VERT
Y1, Y2, Y3, Y4, Y5, Y6: BU-SMA-V
Z1, Z2, Z3, Z4, Z5, Z6: BU-SMA-E-2SIDE; SMA_EDGE_2SIDE
ZED1: µZ-FCI""; µZ

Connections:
BANK13_00_N: PAD34.1, ZED1.89
BANK13_00_P: PAD33.1, ZED1.87
BANK13_01_N: PAD25.1, ZED1.90
BANK13_01_P: PAD26.1, ZED1.88
BANK13_02_N: PAD28.1, ZED1.93
BANK13_02_P: PAD27.1, ZED1.91
BANK13_03_N: PAD32.1, ZED1.94
BANK13_03_P: PAD31.1, ZED1.92
BANK13_04_N: PAD20.1, ZED1.195
BANK13_04_P: PAD19.1, ZED1.193
BANK13_06_N: PAD21.1, ZED1.199
BANK13_06_P: PAD22.1, ZED1.197
EE_CLK1: R4.1, U1.44, U2.4
EE_CS1: R3.1, U1.45, U2.5
EE_DATA1: R6.2, U1.43, U2.3
FTDI_D+: U1.7, U3.1, USB.D+
FTDI_D-: U1.6, U3.2, USB.D-
FTDI_TCK: U1.13, ZED1.1
FTDI_TDI: U1.14, ZED1.4
FTDI_TDO: U1.15, ZED1.3
FTDI_TMS: U1.16, ZED1.2
GND: C1.2, C2.2, C3.2, C4.2, C5.2, C6.2, C7.2, C8.2, C9.2, C10.2, JP1.3, JP2.4, JP3.3, JP4.3, PAD5.1, PAD11.1, PAD17.1, PAD23.1, PAD29.1, PAD35.1, PAD41.1, PAD47.1, Q1.2, Q1.4, R1.1, U1.4, U1.9, U1.10, U1.11, U1.22, U1.23, U1.35, U1.36, U1.41, U1.47, U1.48, U2.2, U3.3, USB.GND, X1.1, X1.4, X1.7, X2.1, X2.4, X2.7, X3.1, X3.4, X3.7, X4.1, X4.4, X4.7, X5.1, X5.4, X5.7, X6.1, X6.4, X6.7, X7.1, X7.4, X7.7, X8.1, X8.4, X8.7, X9.1, X9.4, X9.7, X10.1, X10.4, X10.7, X11.1, X11.4, X11.7, X12.1, X12.4, X12.7, Y1.2, Y1.3, Y1.4, Y1.5, Y2.2, Y2.3, Y2.4, Y2.5, Y3.2, Y3.3, Y3.4, Y3.5, Y4.2, Y4.3, Y4.4, Y4.5, Y5.2, Y5.3, Y5.4, Y5.5, Y6.2, Y6.3, Y6.4, Y6.5, Z1.2@1, Z1.2@2, Z1.2@3, Z1.2@4, Z2.2@1, Z2.2@2, Z2.2@3, Z2.2@4, Z3.2@1, Z3.2@2, Z3.2@3, Z3.2@4, Z4.2@1, Z4.2@2, Z4.2@3, Z4.2@4, Z5.2@1, Z5.2@2, Z5.2@3, Z5.2@4, Z6.2@1, Z6.2@2, Z6.2@3, Z6.2@4, ZED1.15, ZED1.16, ZED1.21, ZED1.22, ZED1.27, ZED1.28, ZED1.33, ZED1.34, ZED1.39, ZED1.40, ZED1.45, ZED1.46, ZED1.51, ZED1.52, ZED1.65, ZED1.66, ZED1.71, ZED1.72, ZED1.77, ZED1.85, ZED1.86, ZED1.95, ZED1.96, ZED1.115, ZED1.116, ZED1.121, ZED1.122, ZED1.127, ZED1.128, ZED1.133, ZED1.134, ZED1.139, ZED1.140, ZED1.145, ZED1.146, ZED1.151, ZED1.152, ZED1.165, ZED1.166, ZED1.171, ZED1.172, ZED1.177, ZED1.185, ZED1.186, ZED1.191, ZED1.192
JX1_00_N: PAD45.1, ZED1.13
JX1_00_P: PAD46.1, ZED1.11
JX1_01_N: PAD39.1, ZED1.14
JX1_01_P: PAD40.1, ZED1.12
JX1_02_N: PAD43.1, ZED1.19
JX1_02_P: PAD44.1, ZED1.17
JX1_03_N: PAD37.1, ZED1.20
JX1_03_P: PAD38.1, ZED1.18
JX1_04_N: X1.5, ZED1.25
JX1_04_P: X1.6, ZED1.23
JX1_06_N: X1.3, ZED1.31
JX1_06_P: X1.2, ZED1.29
JX1_07_N: X2.3, ZED1.32
JX1_07_P: X2.2, ZED1.30
JX1_09_N: X2.5, ZED1.38
JX1_09_P: X2.6, ZED1.36
JX1_10_N: X5.3, ZED1.43
JX1_10_P: X5.2, ZED1.41
JX1_11_N: X6.3, ZED1.44
JX1_11_P: X6.2, ZED1.42
JX1_12_N: X5.5, ZED1.49
JX1_12_P: X5.6, ZED1.47
JX1_13_N: X6.5, ZED1.50
JX1_13_P: X6.6, ZED1.48
JX1_14_N: Z4.1, ZED1.55
JX1_14_P: Z3.1, ZED1.53
JX1_16_N: X11.5, ZED1.63
JX1_16_P: X11.6, ZED1.61
JX1_17_N: X12.3, ZED1.64
JX1_17_P: X12.2, ZED1.62
JX1_18_N: X11.3, ZED1.69
JX1_18_P: X11.2, ZED1.67
JX1_19_N: X12.5, ZED1.70
JX1_19_P: X12.6, ZED1.68
JX1_23_N: Y4.1, ZED1.84
JX1_23_P: Y3.1, ZED1.82
JX2_00_N: PAD7.1, ZED1.119
JX2_00_P: PAD8.1, ZED1.117
JX2_01_N: PAD3.1, ZED1.120
JX2_01_P: PAD4.1, ZED1.118
JX2_02_N: Y6.1, ZED1.125
JX2_02_P: Y5.1, ZED1.123
JX2_03_N: PAD1.1, ZED1.126
JX2_03_P: PAD2.1, ZED1.124
JX2_04_N: X3.5, ZED1.131
JX2_04_P: X3.6, ZED1.129
JX2_05_N: X4.3, ZED1.132
JX2_05_P: X4.2, ZED1.130
JX2_06_N: X3.3, ZED1.137
JX2_06_P: X3.2, ZED1.135
JX2_07_N: X4.5, ZED1.138
JX2_07_P: X4.6, ZED1.136
JX2_08_N: PAD10.1, ZED1.143
JX2_08_P: PAD9.1, ZED1.141
JX2_09_N: Z6.1, ZED1.144
JX2_09_P: Z5.1, ZED1.142
JX2_10_N: X7.5, ZED1.149
JX2_10_P: X7.6, ZED1.147
JX2_11_N: X8.5, ZED1.150
JX2_11_P: X8.6, ZED1.148
JX2_12_N: X7.3, ZED1.155
JX2_12_P: X7.2, ZED1.153
JX2_13_N: X8.3, ZED1.156
JX2_13_P: X8.2, ZED1.154
JX2_15_N: Z1.1, ZED1.164
JX2_15_P: Z2.1, ZED1.162
JX2_16_N: X10.5, ZED1.169
JX2_16_P: X10.6, ZED1.167
JX2_17_N: X9.3, ZED1.170
JX2_17_P: X9.2, ZED1.168
JX2_18_N: X10.3, ZED1.175
JX2_18_P: X10.2, ZED1.173
JX2_19_N: X9.5, ZED1.176
JX2_19_P: X9.6, ZED1.174
JX2_20_N: Y1.1, ZED1.183
JX2_20_P: Y2.1, ZED1.181
JX2_21_N: PAD15.1, ZED1.184
JX2_21_P: PAD16.1, ZED1.182
JX2_23_N: PAD13.1, ZED1.190
JX2_23_P: PAD14.1, ZED1.188
unnamed: R5.1, R6.1, U2.1
unnamed: C1.1, Q1.1, U1.1
unnamed: C2.1, Q1.3, U1.2
unnamed: C3.1, R2.1, U1.34
unnamed: R1.2, U1.5
unnamed: U3.4, USB.ID
PMOD_A_VCC: JP1.1, PAD6.1, PAD12.1
PMOD_B_VCC: JP2.1, PAD18.1, PAD24.1
PMOD_C_VCC: JP3.2, PAD30.1, PAD36.1
PMOD_D_VCC: JP4.2, PAD42.1, PAD48.1
VBUS: C4.1, FB1.1, U3.5, USB.VBUS
VCCA: C6.1, U1.37
VCCD: FB2.1, FB3.1, R2.2, R3.2, R4.2, R5.2, U1.12, U1.24, U1.39, U1.46, U2.6
VCCO_13: JP2.2, ZED1.198
VCCO_34: JP3.1, ZED1.78, ZED1.79, ZED1.80
VCCO_35: JP2.3, ZED1.178, ZED1.179, ZED1.180
VCORE: C5.1, U1.38
VIN_HDR: JP1.2, JP4.1, ZED1.57, ZED1.58, ZED1.59, ZED1.60, ZED1.112, ZED1.157, ZED1.158, ZED1.159, ZED1.160
VPHY: C7.1, C8.1, FB2.2, U1.3
VPLL: C9.1, C10.1, FB3.2, U1.8
VREGIN: FB1.2, U1.40

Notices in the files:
boards/qad-center-v0.8.6.brd:
Copyright (C) 2013 H.Poetzl
Licensed under CERN OHL v.1.1
boards/sensor_frontend_test_v0.5.brd:
Copyright (C) 2015 Herbert Pötzl
Licensed under CERN OHL v.1.2
microzed_breakout_v0.6-default.e833927a.brd:
Copyright (C) 2014 H.Poetzl
parts and their libraries:
SparkFun-FreqCtrl: Licensing: CC v3.0 Share-Alike You are welcome to use this library for commercial purposes.
microbuilder: This work is placed in the public domain, and may be freely used for commercial and non-commercial work with the following conditions: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
